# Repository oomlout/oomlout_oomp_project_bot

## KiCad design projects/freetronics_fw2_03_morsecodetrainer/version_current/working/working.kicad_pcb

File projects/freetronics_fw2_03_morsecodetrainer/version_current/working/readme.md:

# FW2-03-MorseCodeTrainer by freetronics  
This is a harvested standardized copy of a project from github.  
The original project can be found at:  
https://github.com/freetronics/FW2-03-MorseCodeTrainer  
Please consult that link for additional, details, files, and license information.  
Note: It was auto harvested and if the original repo had more than one board file or anything out of the ordinary the files here are likely not representative.

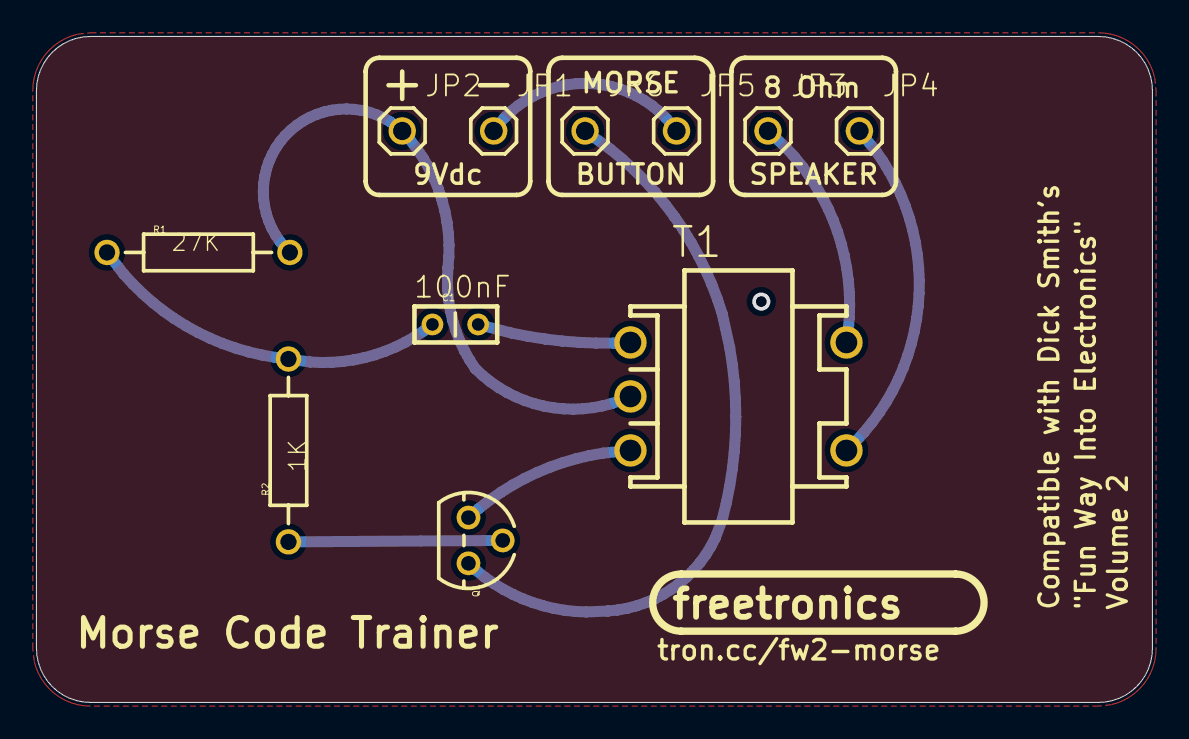
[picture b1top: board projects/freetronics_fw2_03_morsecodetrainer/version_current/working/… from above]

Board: 6 copper layers, 62.0 x 37.0 mm, 11 parts (0 on the bottom side), 9 nets.

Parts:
C1: 0.15uF; CAP-PTH-SMALL
JP1, JP5, JP6: PWR-; 1X01
JP2: PWR+; 1X01
JP3: SPKR+; 1X01
JP4: SPKR-; 1X01
Q1: BC547; TO-92
R1: 27K; FREETRONICS_AXIAL-0.4
R2: 1K; FREETRONICS_AXIAL-0.4
T1: 1K / 8 Ohm; TRANS350MW

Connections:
GND: JP4.1, T1.4
unnamed: JP3.1, T1.5
unnamed: JP2.1, R1.P$2, T1.2
unnamed: C1.2, T1.1
unnamed: Q1.1, T1.3
unnamed: JP1.1, JP5.1
unnamed: JP6.1, Q1.3
unnamed: C1.1, R1.P$1, R2.P$2
unnamed: Q1.2, R2.P$1

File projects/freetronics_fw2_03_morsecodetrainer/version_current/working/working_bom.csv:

"Id";"Designator";"Footprint";"Quantity";"Designation";"Supplier and ref";
1;"JP3";"1X01";1;"SPKR+";;;
2;"T1";"TRANS350MW";1;"1K / 8 Ohm";;;
3;"JP2";"1X01";1;"PWR+";;;
4;"C1";"CAP-PTH-SMALL";1;"0.15uF";;;
5;"R2";"FREETRONICS_AXIAL-0.4";1;"1K";;;
6;"R1";"FREETRONICS_AXIAL-0.4";1;"27K";;;
7;"Q1";"TO-92";1;"BC547";;;
8;"JP6,JP5,JP1";"1X01";3;"PWR-";;;
9;"JP4";"1X01";1;"SPKR-";;;

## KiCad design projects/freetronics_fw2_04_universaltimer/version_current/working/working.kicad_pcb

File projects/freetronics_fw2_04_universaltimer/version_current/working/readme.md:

# OOMP Project  
## FW2-04-UniversalTimer  by freetronics  
  
oomp key: oomp_projects_flat_freetronics_fw2_04_universaltimer  
(snippet of original readme)  
  
Universal Timer  
===============  
Copyright 2016 Freetronics Pty Ltd    
Freetronics site:  http://www.freetronics.com.au    
Freetronics email: <info@freetronics.com>    
  
Based on the project "Universal Timer" described in the book  
"Funway Into Electronics Volume 2" by Dick Smith.  
  
Simple timer based on a 555.  
  
More information is available at:  
  
  http://www.freetronics.com.au/fw2-timer    

INSTALLATION  
------------  
The design is saved as an EAGLE project. EAGLE PCB design software is  
available from www.cadsoftusa.com free for non-commercial use. To use  
this project download it and place the directory containing these files  
into the "eagle" directory on your computer.  

DISTRIBUTION  
------------  
The specific terms of distribution of this project are governed by the  
license referenced below.  

LICENSE  
-------  
Licensed under the TAPR Open Hardware License (www.tapr.org/OHL).  
The "license" folder within this repository also contains a copy of  
this license in plain text format.  
  
  full source readme at [readme_src.md](readme_src.md)  
  
source repo at: [https://github.com/freetronics/FW2-04-UniversalTimer](https://github.com/freetronics/FW2-04-UniversalTimer)  
## Board  

## Schematic  

[schematic pdf](working_schematic.pdf)  
## Images

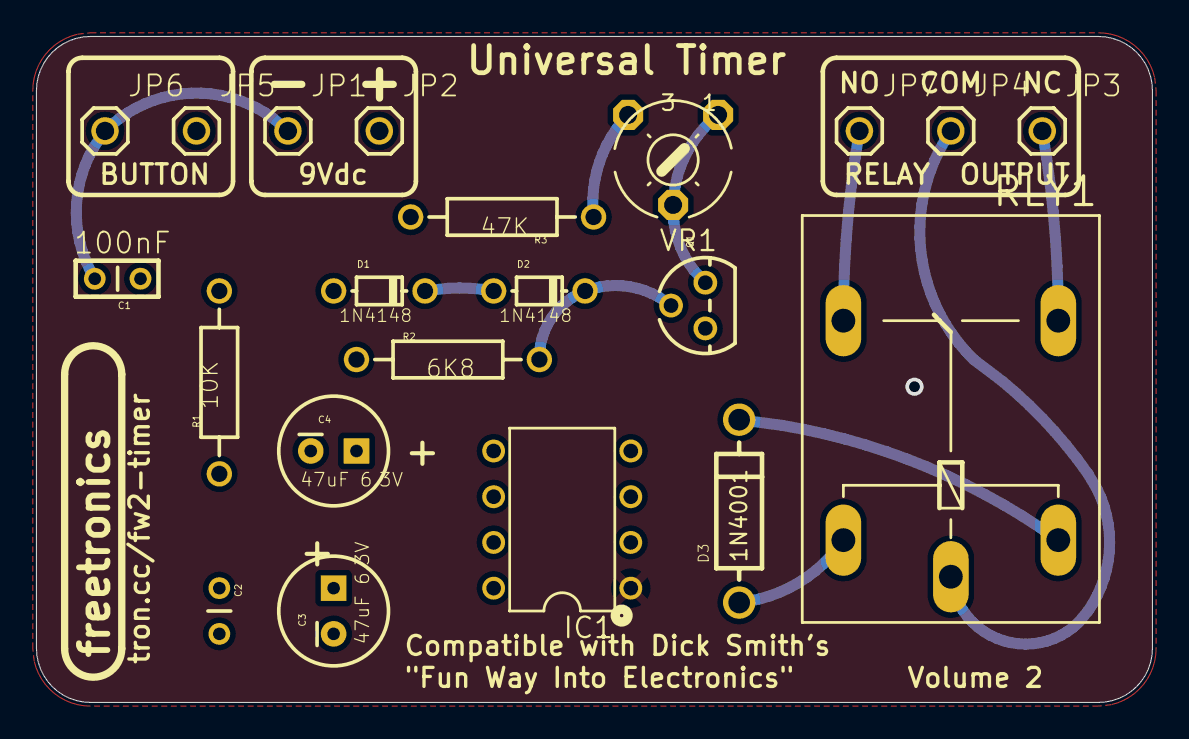
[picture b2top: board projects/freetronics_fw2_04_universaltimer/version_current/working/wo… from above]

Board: 6 copper layers, 62.0 x 37.0 mm, 21 parts (0 on the bottom side), 12 nets.

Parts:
C1, C2: 100nF; CAP-PTH-SMALL
C3, C4: 47uF 6.3V; CPOL-RADIAL-10UF-25V
D1, D2: 1N4148; DIODE-1N914
D3: 1N4001; DIODE-1N4001
IC1: LM555N; DIL08
JP1, JP5, JP6: PWR-; 1X01
JP2: PWR+; 1X01
JP3: SPKR+; 1X01
JP4, JP7: SPKR-; 1X01
Q1: BC557; TO-92
R1: 10K; FREETRONICS_AXIAL-0.4
R2: 6K8; FREETRONICS_AXIAL-0.4
R3: 47K; FREETRONICS_AXIAL-0.4
RLY1: G5LE
VR1: 1M; 6MM

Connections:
unnamed: C3.1, C4.1, Q1.1
unnamed: C1.2, C2.2, C3.2, C4.2, D3.A, JP1.1, JP6.1, R2.P$1, RLY1.2
unnamed: D3.C, RLY1.1
unnamed: JP4.1, RLY1.P
unnamed: JP3.1, RLY1.S
unnamed: JP7.1, RLY1.O
unnamed: C2.1, JP5.1, R1.P$1
unnamed: D2.C, Q1.2, R2.P$2
unnamed: Q1.3, VR1.A, VR1.S
unnamed: D1.A, JP2.1, R1.P$2, R3.P$2
unnamed: R3.P$1, VR1.E
unnamed: D1.C, D2.A

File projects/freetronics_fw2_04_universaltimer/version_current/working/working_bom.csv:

"Id";"Designator";"Footprint";"Quantity";"Designation";"Supplier and ref";
1;"C1,C2";"CAP-PTH-SMALL";2;"100nF";;;
2;"JP6,JP5,JP1";"1X01";3;"PWR-";;;
3;"D3";"DIODE-1N4001";1;"1N4001";;;
4;"JP2";"1X01";1;"PWR+";;;
5;"D1,D2";"DIODE-1N914";2;"1N4148";;;
6;"JP3";"1X01";1;"SPKR+";;;
7;"VR1";"6MM";1;"1M";;;
8;"JP4,JP7";"1X01";2;"SPKR-";;;
9;"R3";"FREETRONICS_AXIAL-0.4";1;"47K";;;
10;"R2";"FREETRONICS_AXIAL-0.4";1;"6K8";;;
11;"C3,C4";"CPOL-RADIAL-10UF-25V";2;"47uF 6.3V";;;
12;"IC1";"DIL08";1;"LM555N";;;
13;"R1";"FREETRONICS_AXIAL-0.4";1;"10K";;;
14;"Q1";"TO-92";1;"BC557";;;
15;"RLY1";"G5LE";1;"G5LE";;;

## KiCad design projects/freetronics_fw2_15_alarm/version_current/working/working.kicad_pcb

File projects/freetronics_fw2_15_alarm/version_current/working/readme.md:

# OOMP Project  
## FW2-15-Alarm  by freetronics  
  
oomp key: oomp_projects_flat_freetronics_fw2_15_alarm  
(snippet of original readme)  
  
Home and Car Alarm  
==================  
Copyright 2016 Freetronics Pty Ltd    
Freetronics site:  http://www.freetronics.com.au    
Freetronics email: <info@freetronics.com>    
  
Based on the project "Home and Car Alarm" described in the book  
"Funway Into Electronics Volume 2" by Dick Smith.  
  
Uses both NO and NC inputs and drives a latched siren output.  
  
More information is available at:  
  
  http://www.freetronics.com.au/fw2-alarm    

INSTALLATION  
------------  
The design is saved as an EAGLE project. EAGLE PCB design software is  
available from www.cadsoftusa.com free for non-commercial use. To use  
this project download it and place the directory containing these files  
into the "eagle" directory on your computer.  

DISTRIBUTION  
------------  
The specific terms of distribution of this project are governed by the  
license referenced below.  

LICENSE  
-------  
Licensed under the TAPR Open Hardware License (www.tapr.org/OHL).  
The "license" folder within this repository also contains a copy of  
this license in plain text format.  
  
  full source readme at [readme_src.md](readme_src.md)  
  
source repo at: [https://github.com/freetronics/FW2-15-Alarm](https://github.com/freetronics/FW2-15-Alarm)  
## Board  

## Schematic  

[schematic pdf](working_schematic.pdf)  
## Images

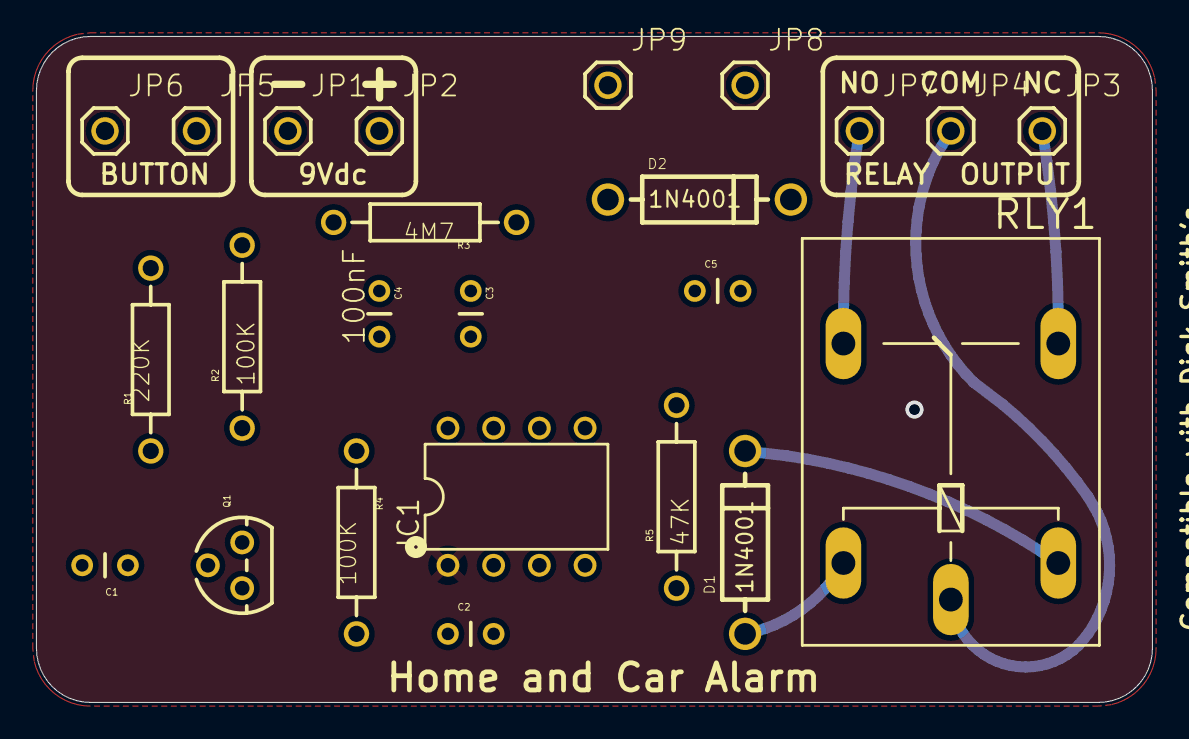
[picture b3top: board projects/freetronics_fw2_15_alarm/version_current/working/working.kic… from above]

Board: 6 copper layers, 62.0 x 37.0 mm, 24 parts (0 on the bottom side), 13 nets.

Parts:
C1, C2, C3, C4, C5: 100nF; CAP-PTH-SMALL
D1, D2: 1N4001; DIODE-1N4001
IC1: LM555N; DIL08
JP1: BAT-; 1X01
JP2: BAT+; 1X01
JP3: SPKR+; 1X01
JP4, JP7: SPKR-; 1X01
JP5, JP6, JP9: PWR-; 1X01
JP8: PWR+; 1X01
Q1: BC547; TO-92
R1: 220K; FREETRONICS_AXIAL-0.4
R2, R4: 100K; FREETRONICS_AXIAL-0.4
R3: 4M7; FREETRONICS_AXIAL-0.4
R5: 47K; FREETRONICS_AXIAL-0.4
RLY1: G5LE

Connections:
unnamed: C3.1, C4.1, R3.P$1
unnamed: C1.2, C3.2, C4.2, C5.2, D1.A, JP1.1, JP9.1, Q1.3, R4.P$1, RLY1.2
unnamed: D1.C, RLY1.1
unnamed: JP6.1, R1.P$2, R2.P$2, R3.P$2
unnamed: JP4.1, RLY1.P
unnamed: JP3.1, RLY1.S
unnamed: JP7.1, RLY1.O
unnamed: C5.1, R5.P$2
unnamed: C1.1, Q1.2, R1.P$1
unnamed: C2.1, Q1.1, R2.P$1, R4.P$2
unnamed: C2.2, R5.P$1
unnamed: D2.A, JP2.1
unnamed: D2.C, JP5.1, JP8.1

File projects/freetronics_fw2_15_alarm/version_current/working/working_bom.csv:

"Id";"Designator";"Footprint";"Quantity";"Designation";"Supplier and ref";
1;"R3";"FREETRONICS_AXIAL-0.4";1;"4M7";;;
2;"JP5,JP9,JP6";"1X01";3;"PWR-";;;
3;"C2,C4,C1,C5,C3";"CAP-PTH-SMALL";5;"100nF";;;
4;"R2,R4";"FREETRONICS_AXIAL-0.4";2;"100K";;;
5;"R1";"FREETRONICS_AXIAL-0.4";1;"220K";;;
6;"JP7,JP4";"1X01";2;"SPKR-";;;
7;"JP1";"1X01";1;"BAT-";;;
8;"JP3";"1X01";1;"SPKR+";;;
9;"IC1";"DIL08";1;"LM555N";;;
10;"R5";"FREETRONICS_AXIAL-0.4";1;"47K";;;
11;"Q1";"TO-92";1;"BC547";;;
12;"D2,D1";"DIODE-1N4001";2;"1N4001";;;
13;"JP2";"1X01";1;"BAT+";;;
14;"RLY1";"G5LE";1;"G5LE";;;
15;"JP8";"1X01";1;"PWR+";;;

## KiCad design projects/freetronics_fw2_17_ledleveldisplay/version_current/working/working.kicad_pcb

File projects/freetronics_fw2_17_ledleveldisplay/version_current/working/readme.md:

# FW2-17-LEDLevelDisplay by freetronics  
This is a harvested standardized copy of a project from github.  
The original project can be found at:  
https://github.com/freetronics/FW2-17-LEDLevelDisplay  
Please consult that link for additional, details, files, and license information.  
Note: It was auto harvested and if the original repo had more than one board file or anything out of the ordinary the files here are likely not representative.

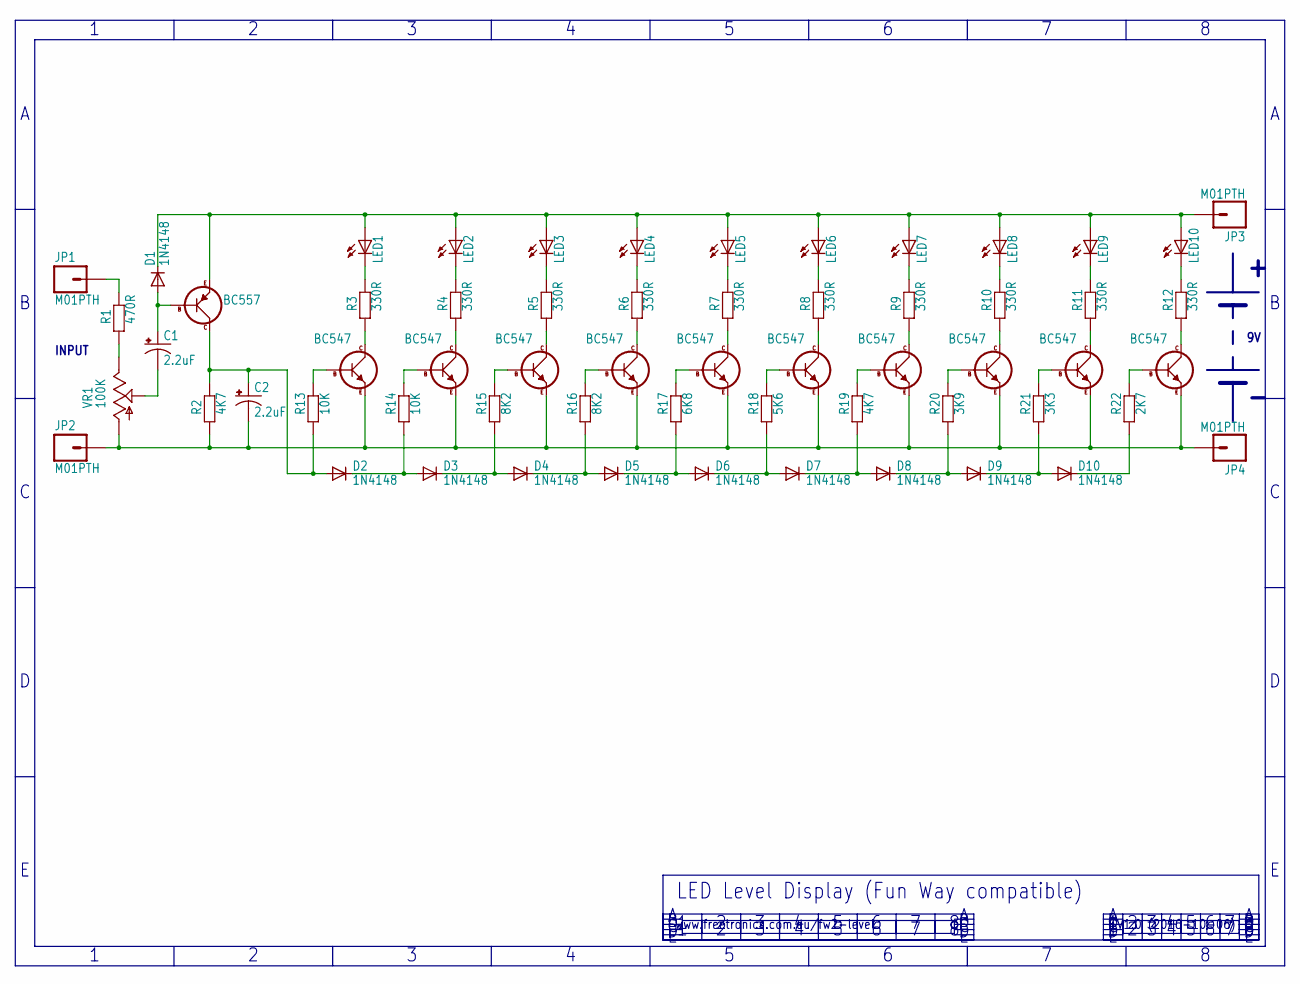
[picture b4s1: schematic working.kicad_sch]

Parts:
C1, C2: 2.2uF; CPOL-RADIAL-100UF-25V
D1, D2, D3, D4, D5, D6, D7, D8, D9, D10: 1N4148; DIODE-1N914L
JP1, JP2, JP3, JP4: M01PTH; 1X01
LED1, LED2, LED3, LED4, LED5, LED6, LED7, LED8, LED9, LED10: LED5MML; LED5MMLARGE
Q1: BC557; TO-92
Q2, Q3, Q4, Q5, Q6, Q7, Q8, Q9, Q10, Q11: BC547; TO-92
R1: 470R; AXIAL-0.4-LARGE
R2: 4K7; AXIAL-0.4-LARGE
R3, R4, R5, R6, R7, R8, R9, R10, R11, R12: 330R; 0309VW
R13, R14: 10K; 0309VW
R15, R16: 8K2; 0309VW
R17: 6K8; 0309VW
R18: 5K6; 0309VW
R19: 4K7; 0309VW
R20: 3K9; 0309VW
R21: 3K3; 0309VW
R22: 2K7; 0309VW
VR1: 100K; 6MM

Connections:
GND: Q2.2 (B), R13.2
unnamed: Q11.2 (B), R22.2
unnamed: D1.C, JP3.1, LED1.A, LED2.A, LED3.A, LED4.A, LED5.A, LED6.A, LED7.A, LED8.A, LED9.A, LED10.A, Q1.3 (E)
unnamed: LED1.K (C), R3.1
unnamed: Q3.1 (C), R4.2
unnamed: C1.1 (+), D1.A, Q1.2 (B)
unnamed: Q3.2 (B), R14.2
unnamed: LED2.K (C), R4.1
unnamed: Q4.1 (C), R5.2
unnamed: LED3.K (C), R5.1
unnamed: D7.C, D8.A, R19.1
unnamed: Q5.1 (C), R6.2
unnamed: C2.1 (+), D2.A, Q1.1 (C), R2.P$2 (2), R13.1
unnamed: D2.C, D3.A, R14.1
unnamed: C2.2 (-), JP2.1, JP4.1, Q2.3 (E), Q3.3 (E), Q4.3 (E), Q5.3 (E), Q6.3 (E), Q7.3 (E), Q8.3 (E), Q9.3 (E), Q10.3 (E), Q11.3 (E), R2.P$1 (1), VR1.A
unnamed: Q4.2 (B), R15.2
unnamed: LED4.K (C), R6.1
unnamed: Q6.1 (C), R7.2
unnamed: LED5.K (C), R7.1
unnamed: Q7.1 (C), R8.2
unnamed: LED6.K (C), R8.1
unnamed: Q8.1 (C), R9.2
unnamed: Q5.2 (B), R16.2
unnamed: Q6.2 (B), R17.2
unnamed: D5.C, D6.A, R17.1
unnamed: D4.C, D5.A, R16.1
unnamed: D3.C, D4.A, R15.1
unnamed: D6.C, D7.A, R18.1
unnamed: D8.C, D9.A, R20.1
unnamed: D9.C, D10.A, R21.1
unnamed: Q7.2 (B), R18.2
unnamed: Q8.2 (B), R19.2
unnamed: Q9.2 (B), R20.2
unnamed: Q10.2 (B), R21.2
unnamed: D10.C, R22.1
unnamed: LED7.K (C), R9.1
unnamed: Q9.1 (C), R10.2
unnamed: LED8.K (C), R10.1
unnamed: Q10.1 (C), R11.2
unnamed: LED9.K (C), R11.1
unnamed: Q11.1 (C), R12.2
unnamed: LED10.K (C), R12.1
unnamed: C1.2 (-), VR1.S
unnamed: R1.P$1 (1), VR1.E
unnamed: JP1.1, R1.P$2 (2)
unnamed: Q2.1 (C), R3.2

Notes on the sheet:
INPUT
www.freetronics.com.au/fw2-level
LED Level Display (Fun Way compatible)
V1.0 (2016-10-06)

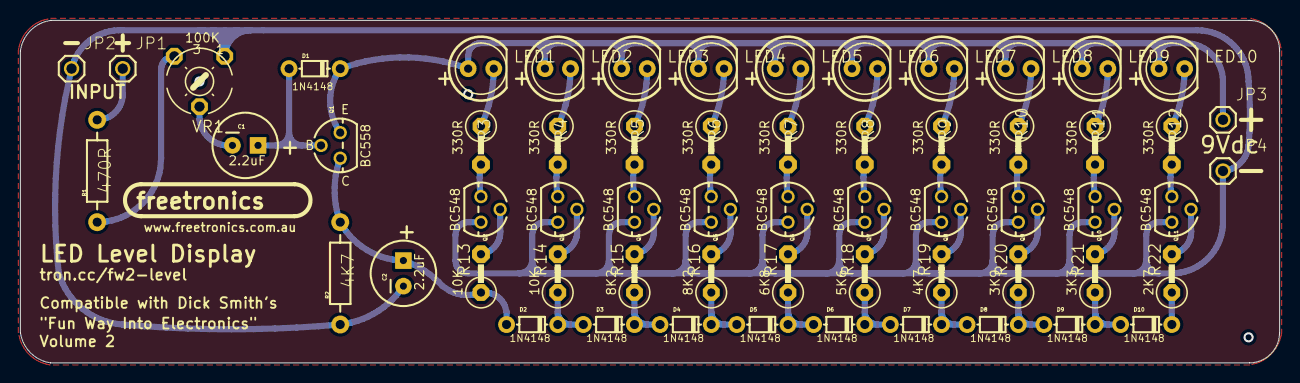
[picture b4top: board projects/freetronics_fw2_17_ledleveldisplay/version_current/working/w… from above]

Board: 6 copper layers, 125.0 x 34.0 mm, 60 parts (0 on the bottom side), 46 nets.

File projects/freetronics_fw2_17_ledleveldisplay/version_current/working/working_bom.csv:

"Id";"Designator";"Footprint";"Quantity";"Designation";"Supplier and ref";
1;"Q4,Q2,Q6,Q9,Q8,Q3,Q7,Q10,Q5,Q11";"TO-92";10;"BC547";;;
2;"C2,C1";"CPOL-RADIAL-100UF-25V";2;"2.2uF";;;
3;"D4,D2,D1,D10,D5,D9,D8,D3,D6,D7";"DIODE-1N914L";10;"1N4148";;;
4;"R16,R15";"0309VW";2;"8K2";;;
5;"LED1,LED8,LED2,LED3,LED4,LED7,LED9,LED10,LED6,LED5";"LED5MMLARGE";10;"";;;
6;"JP2";"1X01";1;"IN-";;;
7;"R11,R10,R3,R7,R9,R8,R6,R4,R5,R12";"0309VW";10;"330R";;;
8;"R13,R14";"0309VW";2;"10K";;;
9;"R17";"0309VW";1;"6K8";;;
10;"R21";"0309VW";1;"3K3";;;
11;"R1";"AXIAL-0.4-LARGE";1;"470R";;;
12;"R19";"0309VW";1;"4K7";;;
13;"R20";"0309VW";1;"3K9";;;
14;"JP3";"1X01";1;"PWR+";;;
15;"JP4";"1X01";1;"PWR-";;;
16;"Q1";"TO-92";1;"BC557";;;
17;"VR1";"6MM";1;"100K";;;
18;"R18";"0309VW";1;"5K6";;;
19;"R2";"AXIAL-0.4-LARGE";1;"4K7";;;
20;"R22";"0309VW";1;"2K7";;;
21;"JP1";"1X01";1;"IN+";;;

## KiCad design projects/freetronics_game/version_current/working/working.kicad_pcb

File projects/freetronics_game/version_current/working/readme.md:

# OOMP Project  
## GAME  by freetronics  
  
oomp key: oomp_projects_flat_freetronics_game  
(snippet of original readme)  
  
Freetronics Game Controller Shield  
==================================  
Copyright 2015 Freetronics Pty Ltd    
Freetronics site:  www.freetronics.com    
Freetronics email: info@freetronics.com    
  
A shield for the Arduino and other microcontroller boards based on the  
same header format, such as the Freetronics Eleven. Include a joystick,  
buttons, a header for a Freetronics 128x128 Pixel OLED Module, and  
a prototyping area.  
  
Safe operation on both 3.3V and 5V Arduino boards.  
  
More information is available on our product page at:  
  
  http://tron.cc/game  
  
INSTALLATION  
------------  
The design is saved as an EAGLE project. EAGLE PCB design software is  
available from www.cadsoftusa.com free for non-commercial use. To use  
this project download it and place the directory containing these files  
into the "eagle" directory on your computer. Then open EAGLE and  
navigate to Projects -> eagle -> GAME.  

DISTRIBUTION  
------------  
The specific terms of distribution of this project are governed by the  
license referenced below.  

LICENSE  
-------  
Licensed under the TAPR Open Hardware License (www.tapr.org/OHL).  
The "license" folder within this repository also contains a copy of  
this license in plain text format.  
  
  full source readme at [readme_src.md](readme_src.md)  
  
source repo at: [https://github.com/freetronics/GAME](https://github.com/freetronics/GAME)  
## Board  

## Schematic  

[schematic pdf](working_schematic.pdf)  
## Images

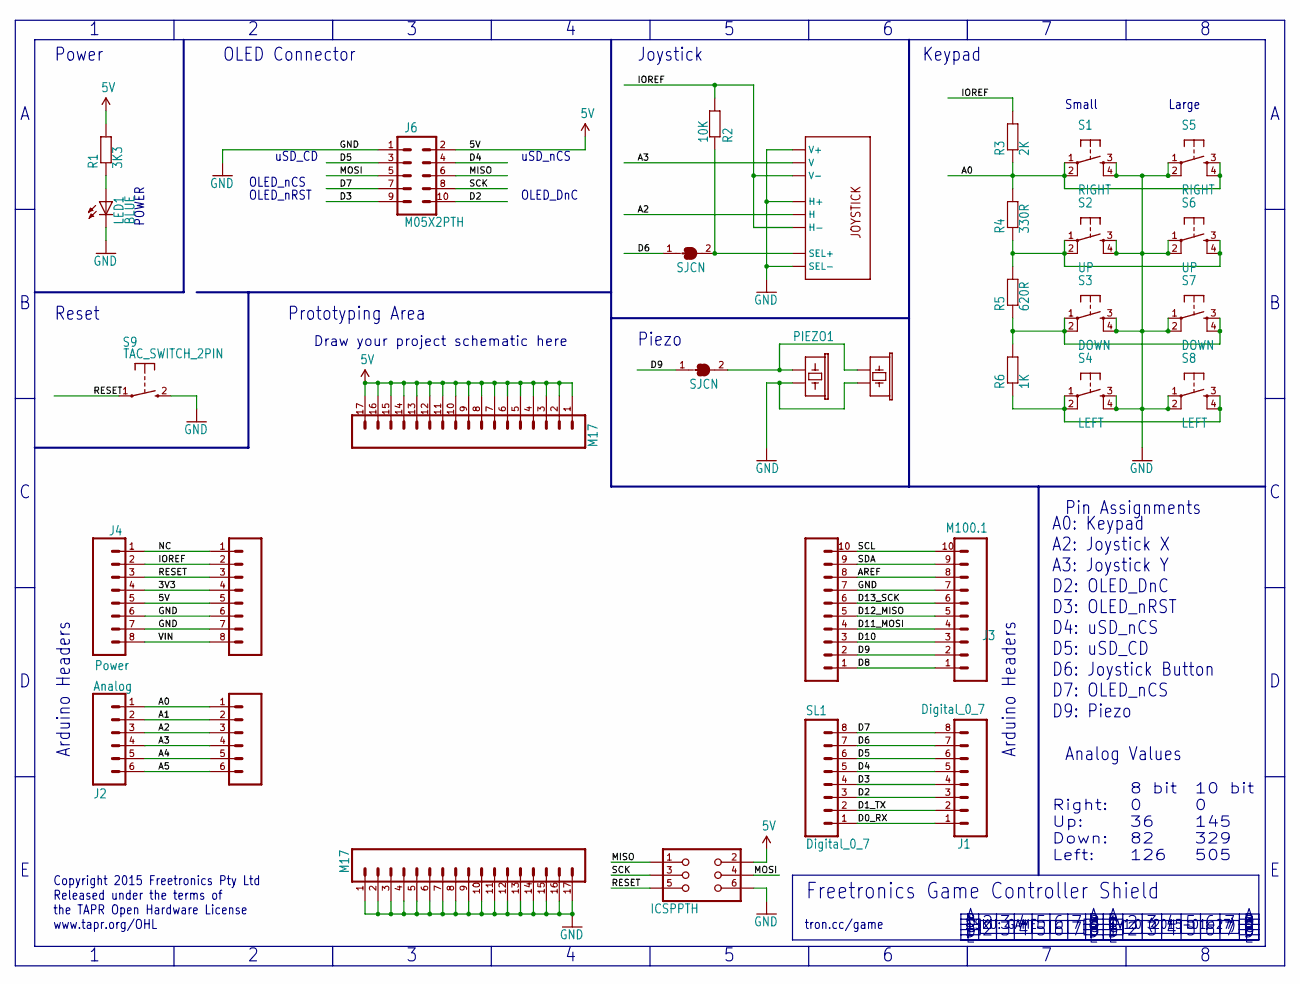
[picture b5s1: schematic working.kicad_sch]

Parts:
J1: Digital_0_7; 1X08
J2: Analog; 1X06
J3: M100.1; 1X10
J4: Power; 1X08
J5: ICSPPTH; 2X03PTH
J6: M05X2PTH; AVR_ICSP
JOY1: JOYSTICKPTH; JOYSTICK
LED1: BLUE; LED-0603
PIEZO1: BUZZERSMD12X12; BUZZER-12X12-SMT
PIEZO2: PIEZO12MM
R1: 3K3; 0603
R2: 10K; 0603
R3: 2K; 0603
R4: 330R; 0603
R5: 620R; 0603
R6: 1K; 0603
S1: RIGHT; TACTILE-PTH
S2: UP; TACTILE-PTH
S3: DOWN; TACTILE-PTH
S4: LEFT; TACTILE-PTH
S5: RIGHT; TACTILE-PTH-12MM
S6: UP; TACTILE-PTH-12MM
S7: DOWN; TACTILE-PTH-12MM
S8: LEFT; TACTILE-PTH-12MM
S9: TAC_SWITCH_2PIN; TACTILE_SWITCH_SMD_2PIN_TINY
SJ1, SJ2: SJCN; SJC
SL1: Digital_0_7; 1X08
SL2: Analog; 1X06
SL3: M100.1; 1X10
SL4: Power; 1X08
SL5, SL6: M17; 1X17

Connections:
3V3: J4.4, SL4.4
5V: J4.5, J5.2, J6.2, R1.2, SL4.5, SL5.1, SL5.2, SL5.3, SL5.4, SL5.5, SL5.6, SL5.7, SL5.8, SL5.9, SL5.10, SL5.11, SL5.12, SL5.13, SL5.14, SL5.15, SL5.16, SL5.17
A0: J2.1, R3.1, R4.2, S1.1, S1.2, S5.3, S5.4, SL2.1
A1: J2.2, SL2.2
A2: J2.3, JOY1.H2 (H), SL2.3
A3: J2.4, JOY1.V2 (V), SL2.4
A4: J2.5, SL2.5
A5: J2.6, SL2.6
AREF: J3.8, SL3.8
D0_RX: J1.1, SL1.1
D1_TX: J1.2, SL1.2
D2: J1.3, J6.10, SL1.3
D3: J1.4, J6.9, SL1.4
D4: J1.5, J6.4, SL1.5
D5: J1.6, J6.3, SL1.6
D6: J1.7, SJ2.1, SL1.7
D7: J1.8, J6.7, SL1.8
D8: J3.1, SL3.1
D9: J3.2, SJ1.1, SL3.2
D10: J3.3, SL3.3
D11_MOSI: J3.4, SL3.4
D12_MISO: J3.5, SL3.5
D13_SCK: J3.6, SL3.6
GND: J3.7, J4.6, J4.7, J5.6, J6.1, JOY1.B2A (SEL-), JOY1.H1 (H+), JOY1.V1 (V+), LED1.C, PIEZO1.1, PIEZO2.2, S1.3, S1.4, S2.3, S2.4, S3.3, S3.4, S4.3, S4.4, S5.1, S5.2, S6.1, S6.2, S7.1, S7.2, S8.1, S8.2, S9.2 (S), SL3.7, SL4.6, SL4.7, SL6.1, SL6.2, SL6.3, SL6.4, SL6.5, SL6.6, SL6.7, SL6.8, SL6.9, SL6.10, SL6.11, SL6.12, SL6.13, SL6.14, SL6.15, SL6.16, SL6.17
IOREF: J4.2, JOY1.H3 (H-), JOY1.V3 (V-), R2.2, R3.2, SL4.2
MISO: J5.1, J6.6
MOSI: J5.4, J6.5
unnamed: LED1.A, R1.1
unnamed: PIEZO1.2, PIEZO2.1, SJ1.2
unnamed: JOY1.B1A (SEL+), R2.1, SJ2.2
unnamed: R6.1, S4.1, S4.2, S8.3, S8.4
unnamed: R5.1, R6.2, S3.1, S3.2, S7.3, S7.4
unnamed: R4.1, R5.2, S2.1, S2.2, S6.3, S6.4
NC: J4.1, SL4.1
RESET: J4.3, J5.5, S9.1, SL4.3
SCK: J5.3, J6.8
SCL: J3.10, SL3.10
SDA: J3.9, SL3.9
VIN: J4.8, SL4.8

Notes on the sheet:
Copyright 2015 Freetronics Pty Ltd Released under the terms of the TAPR Open Hardware License www.tapr.org/OHL
Power
OLED_nCS
Piezo
Analog Values
Keypad
Freetronics Game Controller Shield
Prototyping Area
Reset
uSD_CD
Large
OLED_DnC
tron.cc/game
Draw your project schematic here
Arduino Headers
V1.0 (2015-01-27)
A0: Keypad A2: Joystick X A3: Joystick Y D2: OLED_DnC D3: OLED_nRST D4: uSD_nCS D5: uSD_CD D6: Joystick Button D7: OLED_nCS D9: Piezo
Joystick
uSD_nCS
SKU: GAME
Pin Assignments
10 bit 0 145 329 505
Right: Up: Down: Left:
Small
OLED Connector
8 bit 0 36 82 126
POWER
OLED_nRST

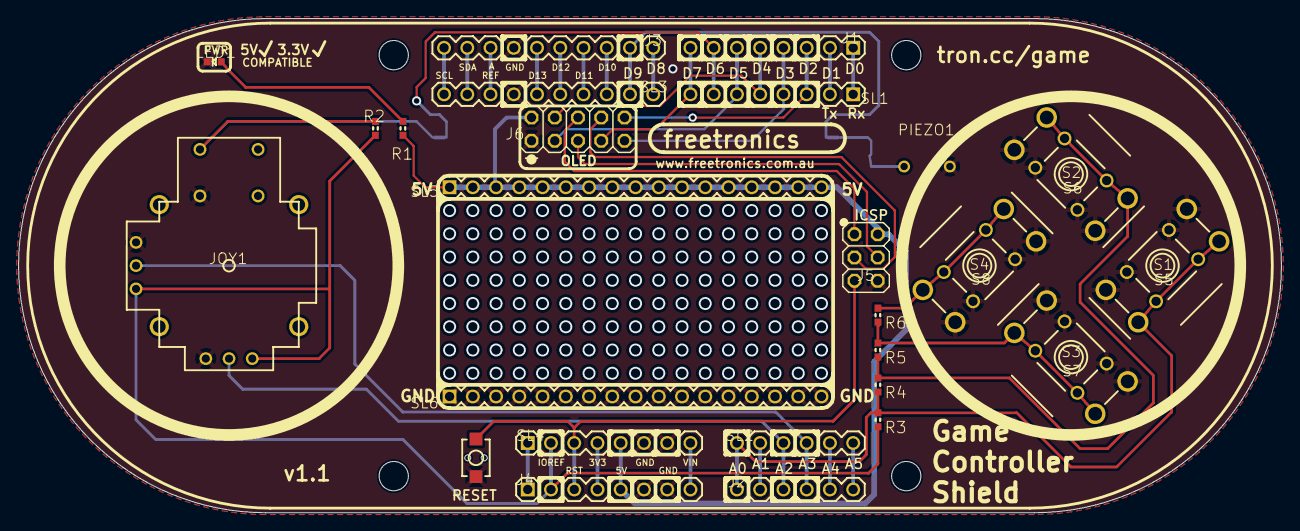
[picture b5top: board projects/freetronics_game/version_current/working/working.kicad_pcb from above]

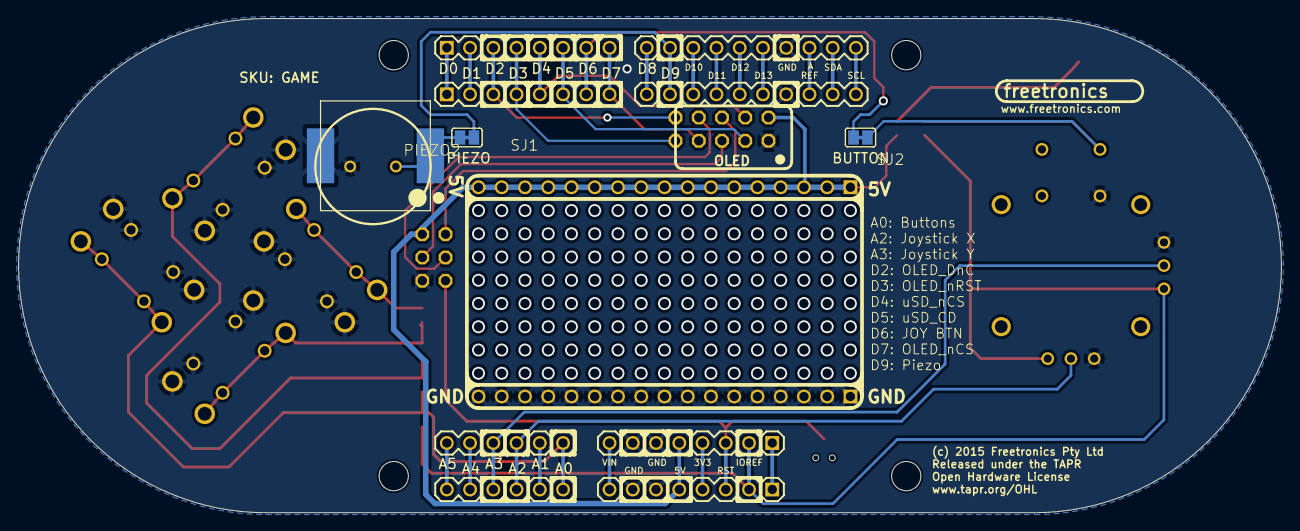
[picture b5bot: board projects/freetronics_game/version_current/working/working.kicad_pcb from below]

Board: 2 copper layers, 138.0 x 54.0 mm, 37 parts (4 on the bottom side), 39 nets.

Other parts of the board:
@HOLE0, @HOLE1, @HOLE2, @HOLE3: (no value)

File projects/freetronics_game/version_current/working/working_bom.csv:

"Id";"Designator";"Footprint";"Quantity";"Designation";"Supplier and ref";
1;"S7";"TACTILE-PTH-12MM";1;"DOWN";;;
2;"S2";"TACTILE-PTH";1;"UP";;;
3;"SL4,J4";"1X08";2;"Power";;;
4;"S8";"TACTILE-PTH-12MM";1;"LEFT";;;
5;"S9";"TACTILE_SWITCH_SMD_2PIN_TINY";1;"TAC_SWITCH_2PIN";;;
6;"SL2,J2";"1X06";2;"Analog";;;
7;"S4";"TACTILE-PTH";1;"LEFT";;;
8;"R2";"0603";1;"10K";;;
9;"R6";"0603";1;"1K";;;
10;"R3";"0603";1;"2K";;;
11;"LED1";"LED-0603";1;"BLUE";;;
12;"J1,SL1";"1X08";2;"Digital_0_7";;;
13;"SL5";"1X17";1;"5V";;;
14;"SL6";"1X17";1;"GND";;;
15;"JOY1";"JOYSTICK";1;"JOYSTICKPTH";;;
16;"SL3,J3";"1X10";2;"Digital_8_13";;;
17;"@HOLE3,@HOLE0,@HOLE2,@HOLE1";"";4;"";;;
18;"J6";"AVR_ICSP";1;"M05X2PTH";;;
19;"J5";"2X03PTH";1;"ICSP";;;
20;"R5";"0603";1;"620R";;;
21;"R4";"0603";1;"330R";;;
22;"S3";"TACTILE-PTH";1;"DOWN";;;
23;"S5";"TACTILE-PTH-12MM";1;"RIGHT";;;
24;"S1";"TACTILE-PTH";1;"RIGHT";;;
25;"R1";"0603";1;"3K3";;;
26;"S6";"TACTILE-PTH-12MM";1;"UP";;;
27;"PIEZO2";"PIEZO12MM";1;"PIEZO12MM";;;
28;"SJ2,SJ1";"SJC";2;"SJCN";;;
29;"PIEZO1";"BUZZER-12X12-SMT";1;"BUZZERSMD12X12";;;

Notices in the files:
projects/freetronics_fw2_03_morsecodetrainer/version_current/working/working.kicad_pcb:
(c) 2016 Freetronics Pty Ltd
projects/freetronics_game/version_current/working/working.kicad_pcb:
(c) 2015 Freetronics Pty Ltd
Open Hardware License
projects/freetronics_gpsmodule/version_current/working/working.kicad_pcb:
(C)2014 Freetronics P/L
projects/freetronics_gsmgpsshield/version_current/working/working.kicad_pcb:
Copyright 2014 Freetronics Pty Ltd
